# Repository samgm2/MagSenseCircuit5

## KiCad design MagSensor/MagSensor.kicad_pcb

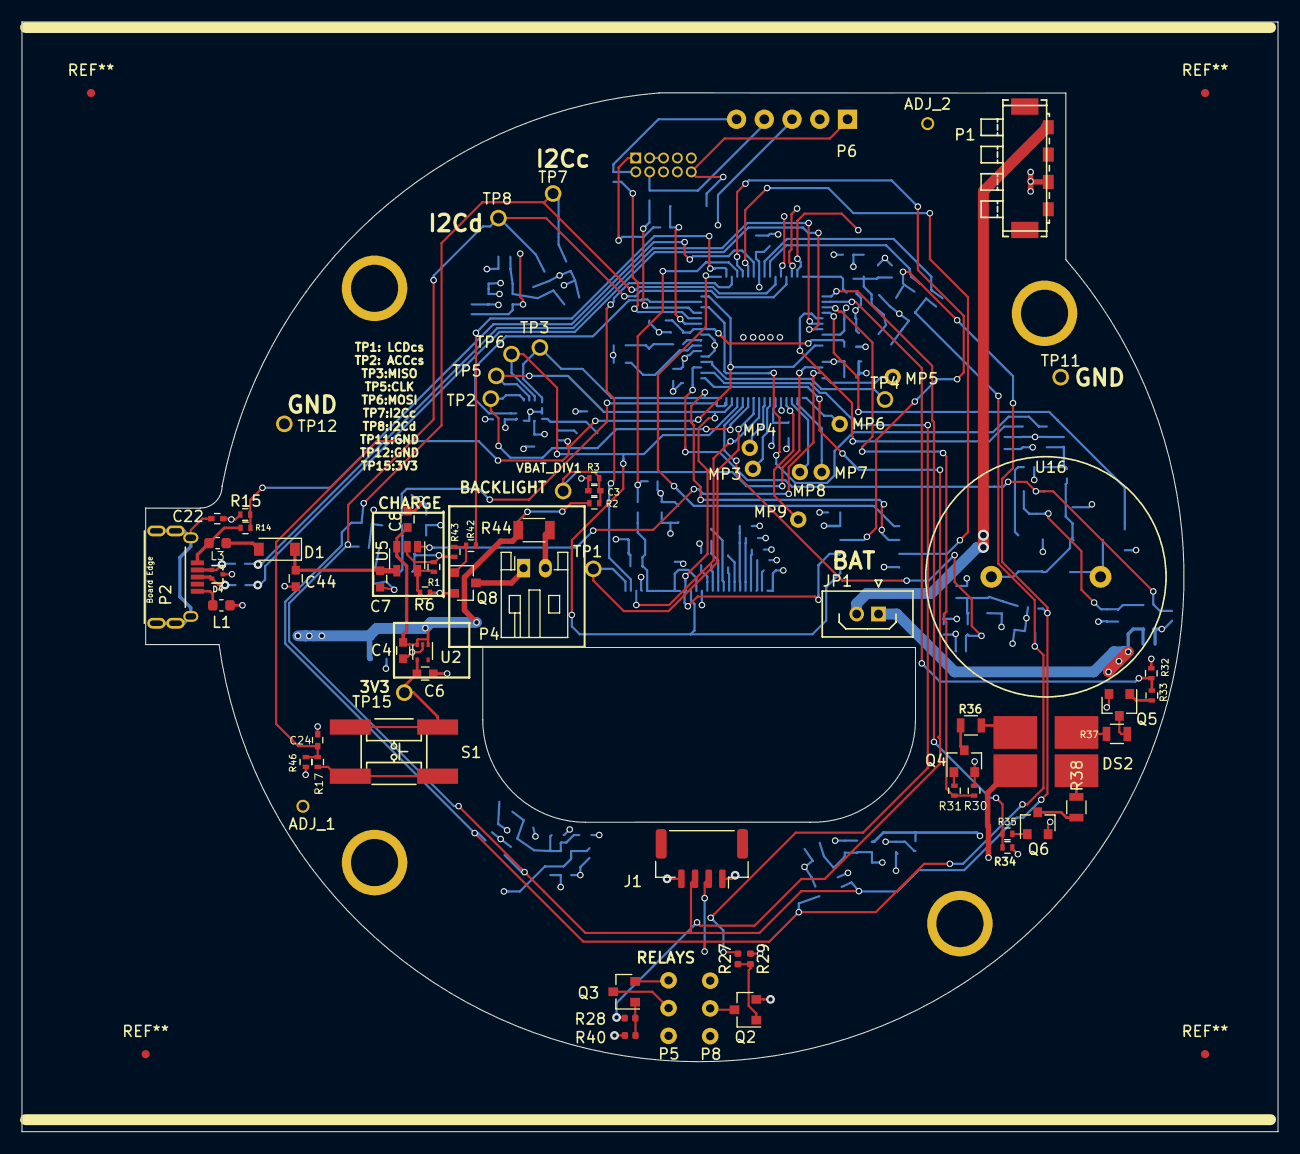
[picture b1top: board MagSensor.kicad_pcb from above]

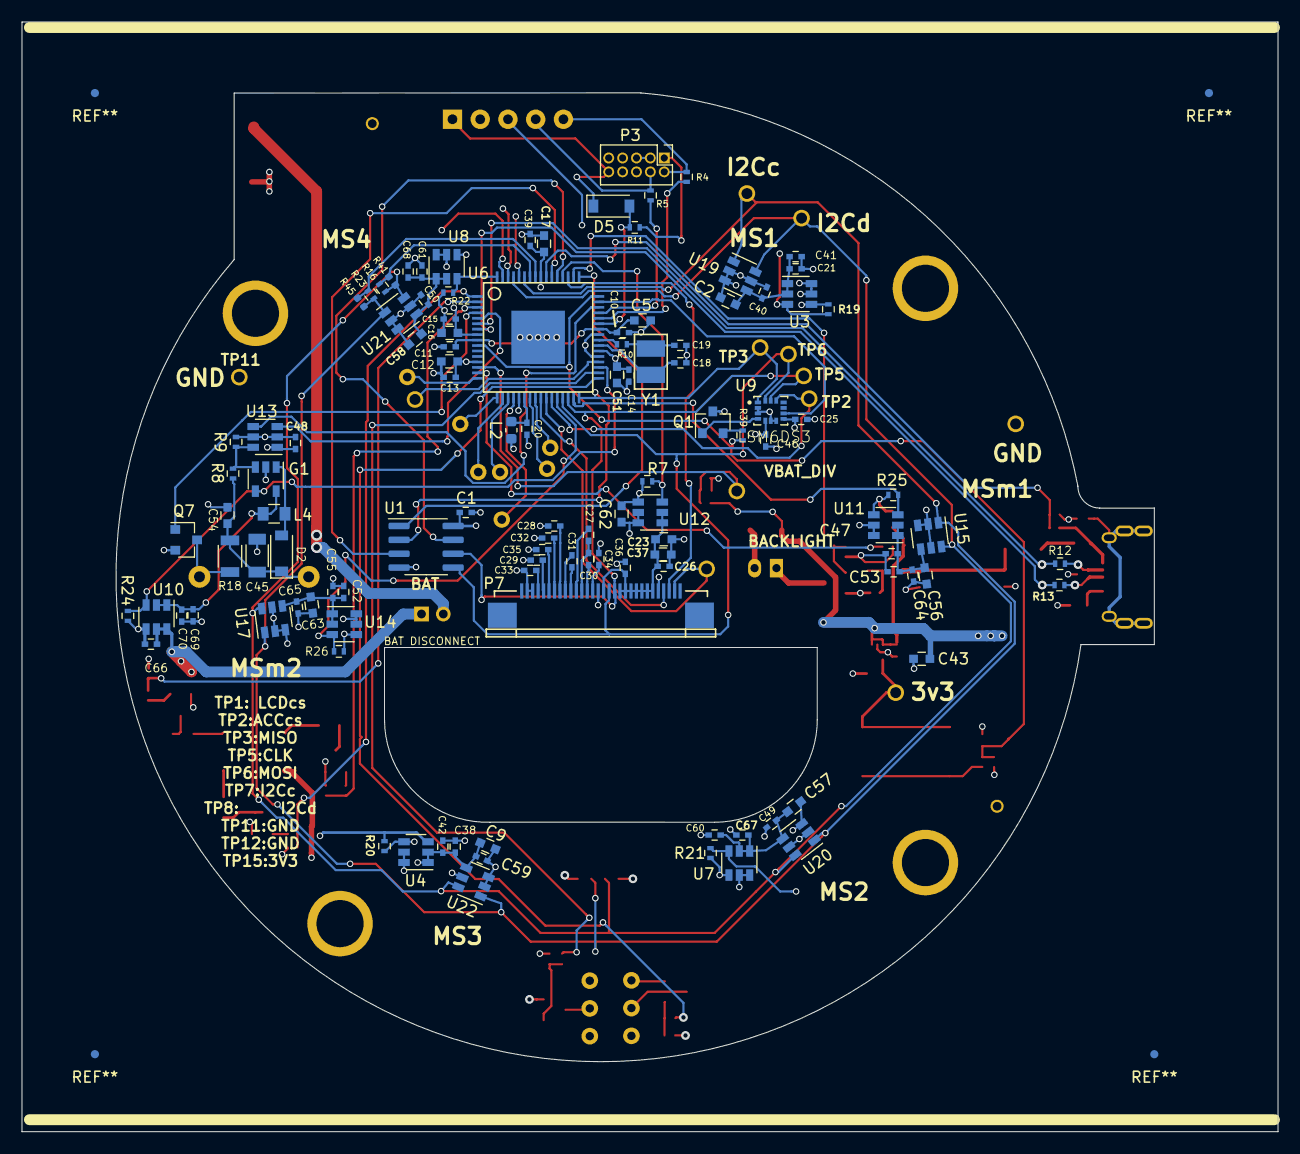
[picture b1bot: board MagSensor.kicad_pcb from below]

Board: 4 copper layers, 115.0 x 101.6 mm, 192 parts (112 on the bottom side), 111 nets.

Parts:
ADJ_1, ADJ_2: FIDUCIAL; FiducialSam1
C1, C10, C11, C13, C14, C15, C20, C21, C22, C24, C25, C26, C36, C38, C39, C40, C46, C47, C48, C49, C50, C52, C59, C60, C61, C64, C65, C69: 0.1uF; C_0402
C2, C4, C5, C6, C7, C8, C9, C12, C16, C17, C23, C37, C43, C44, C51, C56, C57, C58, C62, C63: 4.7uF; C_0603
C3, C27, C28, C29, C30, C31, C32, C33, C34, C35, C41, C42, C53, C55, C66, C67, C68, C70: 1uF; C_0402
C18, C19: 15pF; C_0402
C45: TBD (50v) (DNP); C_1206
C54: 1uF (50v); C_0603
D1, D5: MBR0520LT1G; D_SOD-123
D2: D_Schottky; D_SOD-123
D4: ESD5V3U2U; SOT-723
DS2: CLVBA_RGB_LED; CLVBA
G1: AP3012; SOT-23-5
J1: Conn_01x04; JST_GH_SM04B-GHS-TB_1x04-1MP_P1.25mm_Horizontal
JP1: M22-2510246 {SPN02SYBN-RC}; Harwin_LTek-Male_02x2.00mm_Straight
L1, L2, L3: BLM18PG600; L_0603_1608Metric
L4: 10uH; C_0805
MNT1, MNT2, MNT3, MNT4: MNT; N8-Screw
MP3, MP4, MP5, MP6, MP7, MP8, MP9: TEST; Measurement_Point_Round-TH_Small
P1: 009155004541006; BatCon_009155004541006
P2: USB_Micro B; 1054431101
P3: PGM_DBG; Pin_Header_Straight_2x05_Pitch1.27mm
P4: ER-CON2.0-2P-SMD; JST_PH_S2B-PH-K_02x2.00mm_Angled
P5, P8: CONN_01X03; 3_50D_100SP_Solder
P6: POGO_PGM; POGO5
P7: SFV30R-4STBE1HLF; SFV30R-4STBE1HLF-Inverted
Q1, Q2, Q3, Q4, Q5, Q6, Q7, Q8: MMBT2222; SOT-23
R1, R6, R9, R14, R16, R23: 4.7K; R_0402
R2, R8, R11, R30, R32, R34, R46: 100K; R_0402
R3, R7, R19, R20, R21, R22, R24, R25, R26: 390K (1%); R_0402
R4, R5, R12, R13: 33; R_0402
R10: 499; R_0402
R15, R17, R31, R33, R35, R39, R42, R43: 10K; R_0402
R18: 4.7K; R_1206
R27, R28, R29, R40: 10K; R_0402_1005Metric
R36, R37, R38: 124; R_0805
R41, R45: 4.7K; R_0402_1005Metric
R44: 49.9; R_1206
S1: TL3301; ESwitch_TL3301+Gull+J
TP1: LCDcs; TP_Pin40
TP2: IMUcs; TP_Pin40
TP3: MISO; TP_Pin40
TP4, TP5: SPICLK; TP_Pin40
TP6: MOSI; TP_Pin40
TP7: I2C0_C; TP_Pin40
TP8: I2C_D; TP_Pin40
TP11, TP12: GND; TP_Pin40
TP15: 3V3; TP_Pin40
U1: AT25xxx; SOIC-8_3.9x4.9mm_P1.27mm
U2: TCR2EE/EF; SOT-553
U3, U4, U7, U8, U10, U11, U12, U14: SiP32510; SOT-23-6
U5: MCP73831-2AC; SOT-23-5
U6: XMC4200-F64; XMC4200-64LQFP
U9: LSM6DS3; PQFN50P300X250X86-14N
U13: MCP4012T-503E/CH; SOT-23-6
U15, U17, U19, U20, U21, U22: TLV493D; SOT-23-6
U16: PiezoTransducer; Piezo_22mm_7mm_4KHz
VBAT_DIV1: TEST; TP_Pin40
Y1: 12MHz; Crystal_NX3225

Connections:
+3V3: C1.1, C6.1, C12.1, C13.1, C14.1, C15.1, C16.1, C17.1, C25.2, C39.1, C46.2, C48.1, C51.1, C62.1, J1.1, L2.1, P3.1, P6.3, Q1.3, R11.1, S1.3, S1.4, TP15.1, U1.8, U2.4, U3.5, U3.6, U4.5, U4.6, U6.8, U6.13, U6.38, U6.56, U7.5, U7.6, U8.5, U8.6, U9.5, U9.8, U11.5, U11.6, U12.5, U12.6, U13.1, U14.5, U14.6
+BATT: C4.1, C8.2, C43.1, C66.1, DS2.2, JP1.1, R2.1, R44.1, U2.1, U2.3, U5.3, U10.5, U10.6
+V_chrg: C7.1, C44.1, D1.1, U5.4
/IMU_Wake/HIB_IO: C24.2, R17.1, R39.1, R46.1, U6.10, U6.48
/IMU_Wake/IMU_INTTERRUPT2: U6.47, U9.9
/IMU_Wake/SPI_CLK: P7.13, TP5.1, U1.6, U6.30, U9.13
/IMU_Wake/SPI_MISO: TP3.1, U1.2, U6.32, U9.1
/IMU_Wake/SPI_MOSI: P7.14, TP6.1, U1.5, U6.29, U9.14
/IMU_Wake/~IMU_CS: TP2.1, U6.27, U9.12
/LCD/LCD_A0: P7.4, U6.25
/LCD/LCD_BACKLIGHT: R42.2, U6.50
/LCD/LCD_EN: R7.1, U6.52, U12.3
/LCD/~LCD_CS: P7.2, TP1.1, U6.26
/LCD/~LCD_RESET: P7.3, U6.51
/LEDs/LED_BLU: R34.1, R35.2, U6.1
/LEDs/LED_GRN: R32.1, R33.2, U6.2
/LEDs/LED_RED: R30.1, R31.2, U6.3
/Piezo/PZ: Q7.1, U6.4
/Piezo/PZ_EN: G1.4, R24.1, U6.35, U10.3
/Piezo/V_Piezo: C45.1, C54.1, D2.1, R8.1, R18.1, U16.1
/Piezo/vPU~D: U6.5, U13.3
/Piezo/~vPCS: U6.46, U13.4
/Power/ChargeStat: U5.1, U6.15
/Power/VBatDiv: C3.1, R2.2, R3.1, U6.14, VBAT_DIV1.1
/Sensors and Interfaces/I2C_0_CLK: J1.2, R23.2, R45.2, TP7.1, U6.59, U15.1, U17.1, U19.1, U20.1, U21.1, U22.1
/Sensors and Interfaces/I2C_0_DTA: J1.3, R16.2, R41.2, TP8.1, U6.61, U15.6, U17.6, U19.6, U20.6, U21.6, U22.6
/Sensors and Interfaces/I2cPuC: R23.1, R45.1, U6.57
/Sensors and Interfaces/I2cPuD: R16.1, R41.1, U6.58
/Sensors and Interfaces/PowerMagSense1: C2.1, C21.1, C40.2, C41.1, U3.1, U3.2, U19.4
/Sensors and Interfaces/PowerMagSense2: C49.2, C57.1, C60.1, C67.1, U7.1, U7.2, U20.4
/Sensors and Interfaces/PowerMagSense3: C9.1, C38.1, C42.1, C59.2, U4.1, U4.2, U22.4
/Sensors and Interfaces/PowerMagSense4: C50.2, C58.1, C61.1, C68.1, U8.1, U8.2, U21.4
/Sensors and Interfaces/PowerMagSenseM1: C47.1, C53.1, C56.1, C64.2, U11.1, U11.2, U15.4
/Sensors and Interfaces/PowerMagSenseM2: C52.1, C55.1, C63.1, C65.2, U14.1, U14.2, U17.4
/Sensors and Interfaces/RESET: D5.2, R11.2, U6.43
/Sensors and Interfaces/Relay1: R27.2, U6.34
/Sensors and Interfaces/Relay2: R28.2, U6.33
/Sensors and Interfaces/S_PWR1_EN: R19.1, U3.3, U6.60
/Sensors and Interfaces/S_PWR2_EN: R21.1, U6.62, U7.3
/Sensors and Interfaces/S_PWR3_EN: R20.1, U4.3, U6.63
/Sensors and Interfaces/S_PWR4_EN: R22.1, U6.64, U8.3
/Sensors and Interfaces/S_PWR_M1_EN: R25.1, U6.31, U11.3
/Sensors and Interfaces/S_PWR_M2_EN: R26.1, U6.28, U14.3
/Sensors and Interfaces/TCK: R5.1, U6.45
/Sensors and Interfaces/TMS: R4.1, U6.44
/Sensors and Interfaces/USB+: R13.2, U6.7
/Sensors and Interfaces/USB-: R12.2, U6.6
/Sensors and Interfaces/VBUS_DETECT: R14.2, R15.1, U6.55
/xmc4200/VAREF: C20.1, L2.2, U6.22
/xmc4200/~eeCs: U1.1, U6.49
/xmc4200/~eeHold: U1.7, U6.53
/xmc4200/~eeWp: U1.3, U6.54
GND: C1.2, C2.2, C3.2, C4.2, C5.2, C6.2, C7.2, C8.1, C9.2, C10.2, C11.2, C12.2, C13.2, C14.2, C15.2, C16.2, C17.2, C18.2, C19.2, C20.2, C21.2, C22.2, C23.2, C24.1, C25.1, C26.2, C28.1, C29.1, C32.1, C33.1, C34.1, C35.1, C36.2, C37.2, C38.2, C39.2, C40.1, C41.2, C42.2, C43.2, C44.2, C45.2, C46.1, C47.2, C48.2, C49.1, C50.1, C51.2, C52.2, C53.2, C54.2, C55.2, C56.2, C57.2, C58.2, C59.1, C60.2, C61.2, C62.2, C63.2, C64.1, C65.1, C66.2, C67.2, C68.2, C69.2, C70.2, D4.3, G1.2, J1.4, L1.2, P1.3, P3.3, P3.5, P5.3, P6.2, P7.5, P7.16, P7.28, P7.29, P8.3, Q2.2, Q3.2, Q4.2, Q5.2, Q6.2, Q7.2, Q8.2, R1.2, R3.2, R6.2, R7.2, R9.2, R15.2, R19.2, R20.2, R21.2, R22.2, R24.2, R25.2, R26.2, R29.1, R30.2, R32.2, R34.2, R40.1, R43.1, R46.2, TP11.1, TP12.1, U1.4, U2.2, U3.4, U4.4, U5.2, U6.21, U6.37, U6.41, U6.65, U7.4, U8.4, U9.2, U9.3, U9.6, U9.7, U10.4, U11.4, U12.4, U13.2, U13.5, U14.4, U15.2, U15.3, U15.5, U17.2, U17.3, U17.5, U19.2, U19.3, U19.5, U20.2, U20.3, U20.5, U21.2, U21.3, U21.5, U22.2, U22.3, U22.5
unnamed: C5.1, C10.1, C11.1, U6.9, U6.42
unnamed: C18.1, U6.39, Y1.1
unnamed: C19.1, R10.1, Y1.2
unnamed: C22.1, P2.6
unnamed: C23.1, C26.1, C36.1, C37.1, P7.6, P7.7, P7.8, P7.9, P7.10, P7.11, P7.12, P7.15, U12.1, U12.2
unnamed: C27.1, C30.1, P7.19
unnamed: C27.2, P7.20
unnamed: C28.2, P7.23
unnamed: C29.2, P7.26
unnamed: C30.2, P7.18
unnamed: C31.1, P7.22
unnamed: C31.2, P7.21
unnamed: C32.2, P7.24
unnamed: C33.2, P7.27
unnamed: C34.2, P7.17
unnamed: C35.2, P7.25
unnamed: C69.1, C70.1, G1.5, L4.1, U10.1, U10.2
unnamed: D1.2, L3.1
unnamed: D2.2, G1.1, L4.2
unnamed: D4.1, P2.2, R12.1
unnamed: D4.2, P2.3, R13.1
unnamed: D5.1, P3.10, P6.1
unnamed: DS2.1, R36.1
unnamed: DS2.3, R38.1
unnamed: DS2.4, R37.1
unnamed: G1.3, R8.2, R9.1, U13.6
unnamed: JP1.2, P1.1
unnamed: L1.1, P2.5
unnamed: L3.2, P2.1, R14.1
unnamed: MP3.1, U6.23
unnamed: MP4.1, U6.24
unnamed: MP5.1, U6.16
unnamed: MP6.1, U6.17
unnamed: MP7.1, U6.18
unnamed: MP8.1, U6.19
unnamed: MP9.1, U6.20
unnamed: P3.2, P6.5, R4.2
unnamed: P3.4, P6.4, R5.2
unnamed: P4.1, Q8.3
unnamed: P4.2, R44.2
unnamed: P5.2, Q3.3
unnamed: P8.2, Q2.3
unnamed: Q1.1, U9.4
unnamed: Q1.2, R39.2
unnamed: Q2.1, R27.1, R29.2
unnamed: Q3.1, R28.1, R40.2
unnamed: Q4.1, R31.1
unnamed: Q4.3, R36.2
unnamed: Q5.1, R33.1
unnamed: Q5.3, R37.2
unnamed: Q6.1, R35.1
unnamed: Q6.3, R38.2
unnamed: Q7.3, R18.2, U16.2
unnamed: Q8.1, R42.1, R43.2
unnamed: R1.1, R6.1, U5.5
unnamed: R10.2, U6.40
unnamed: R17.2, S1.1, S1.2
unnamed: TP4.1, U6.36

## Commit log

2019-04-28 Customer Release 1
    First circuit release to customers (Formerly MagSensor5b)
2019-10-02 Six sensor system DRC and ERC completed
2019-11-14 AD8293G16 Based design
